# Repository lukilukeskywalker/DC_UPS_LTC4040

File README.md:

# DC_UPS_LTC4040
Low power Uninterrupible Power Supply based on the LTC4040

*The LTC4040 is a complete 3.5V to 5.5V supply rail battery backup system. It contains a high current step-up DC/DC regulator to back up the supply from a single-cell Li-Ion or LiFePO4 battery.*
Picked from the datasheet.

So yeah, This is supposed to be a place in module for Low Power systems that need to keep functioning when power goes off. The dimensions of the module are 30 x 30 mm, and it can be configured (as stated in the datasheet) to support different battery chemistries, and to disable or enable features like Overvoltage protection or Temperature Control of the battery

Everything is described in the schematic:

And the board design is Included:

The board hasn't been tested yet, so take with care. 
Also I do not take any responsability or problems that may arrise with its use

### Proyects that may arrise Interest to the readers:
- [The Ultimate Single Cell Lithium UPS for any Raspberry Pi](https://hackaday.io/project/162653/logs?sort=oldest)
- [LTC4040 5V, 2.5A Uninterruptible Power Supply (UPS) with USB-C](https://www.beyondlogic.org/ltc4040-5v-2-5a-uninterruptible-power-supply-ups-with-usb-c/)

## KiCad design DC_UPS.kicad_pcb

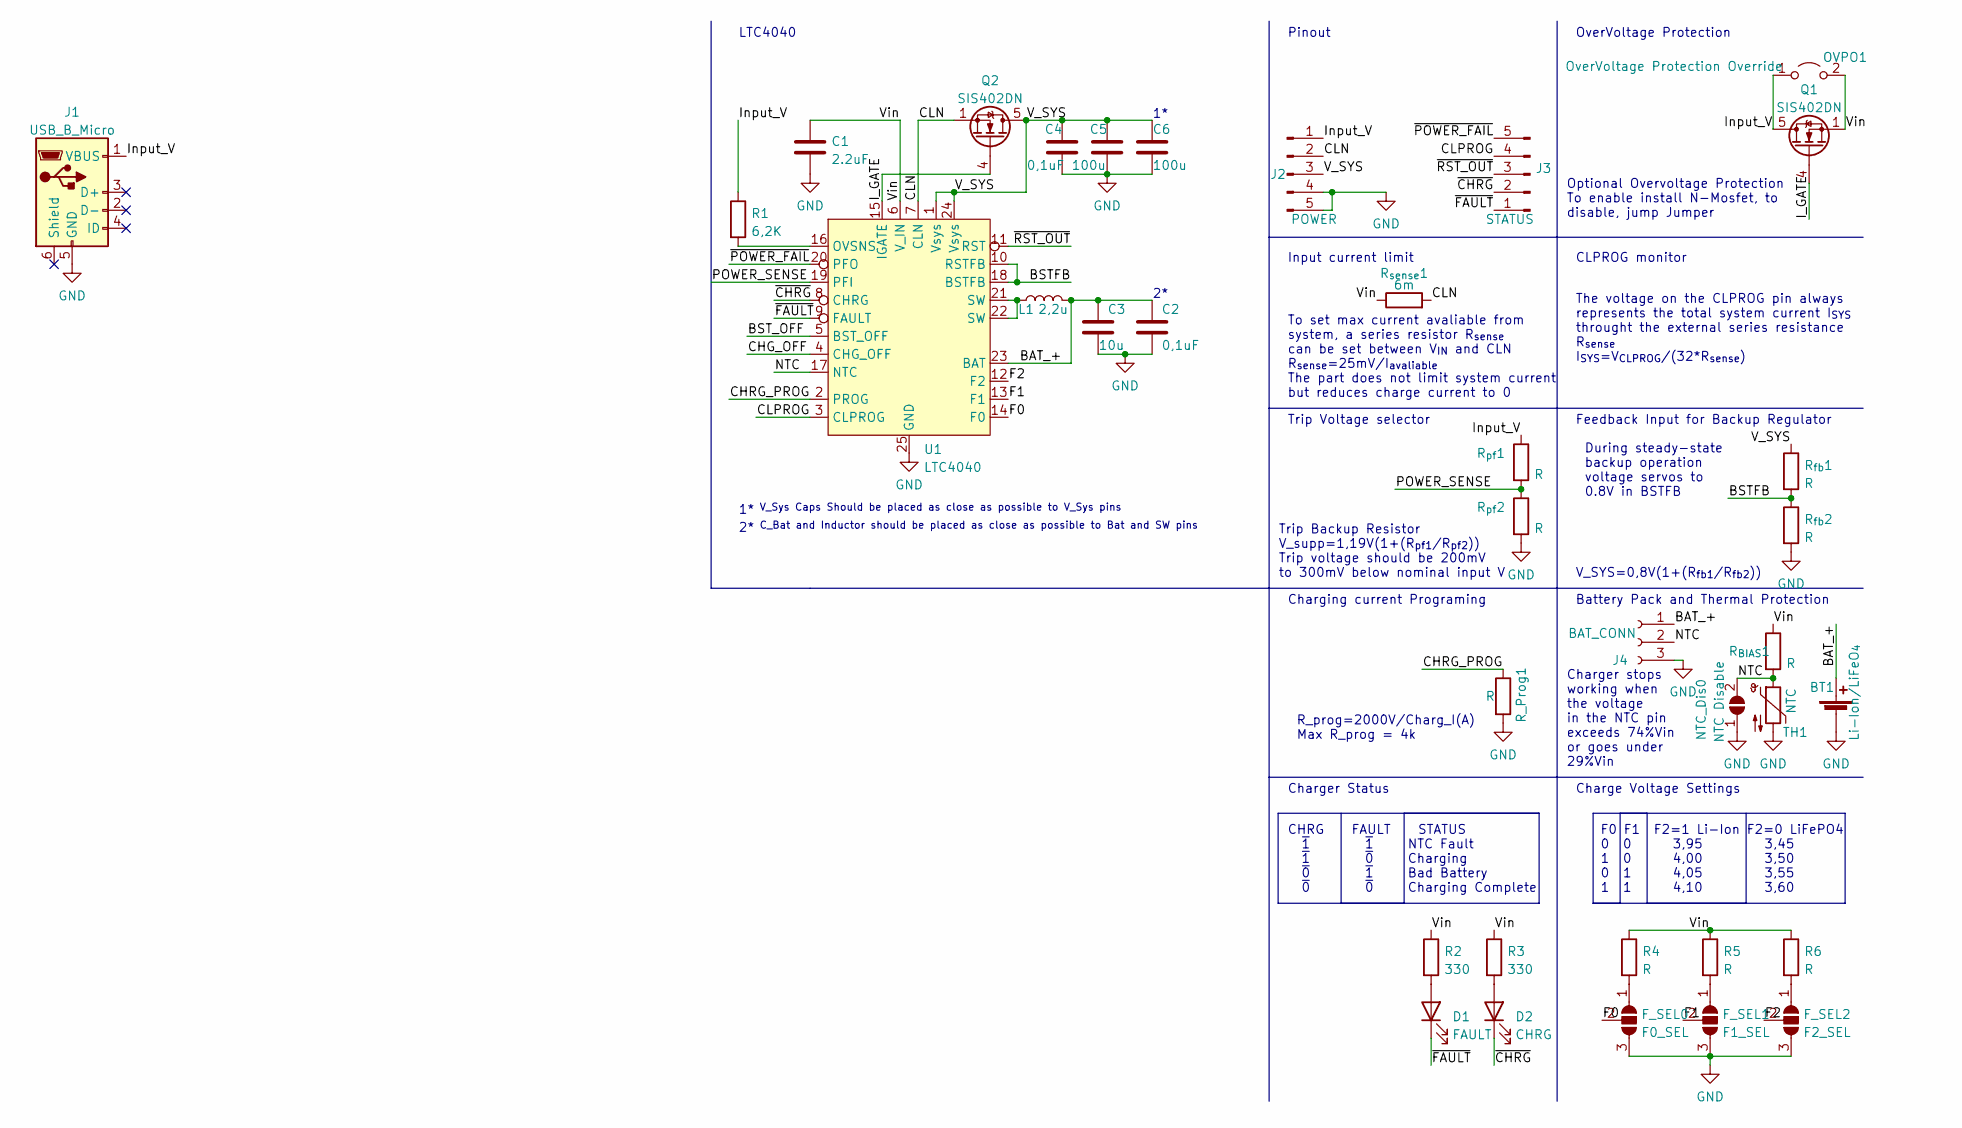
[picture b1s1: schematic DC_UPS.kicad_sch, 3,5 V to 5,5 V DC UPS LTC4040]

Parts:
BT1: Li-Ion/LiFeO_{4}; TE_1776119-2
C1: 2.2uF; C_0402_1005Metric_Pad0.74x0.62mm_HandSolder
C2, C4: 0,1uF; C_0402_1005Metric_Pad0.74x0.62mm_HandSolder
C3: 10u; C_0805_2012Metric_Pad1.18x1.45mm_HandSolder
C5, C6: 100u; C_1206_3216Metric_Pad1.33x1.80mm_HandSolder
D1: FAULT; LED_1206_3216Metric_Pad1.42x1.75mm_HandSolder
D2: CHRG; LED_1206_3216Metric_Pad1.42x1.75mm_HandSolder
F_SEL0: F0_SEL; SolderJumper-3_P1.3mm_Bridged2Bar12_RoundedPad1.0x1.5mm
F_SEL1: F1_SEL; SolderJumper-3_P1.3mm_Bridged2Bar12_RoundedPad1.0x1.5mm
F_SEL2: F2_SEL; SolderJumper-3_P1.3mm_Bridged2Bar12_RoundedPad1.0x1.5mm
J1: USB_B_Micro; TE_2013499-1
J2: POWER; CastellatedPinHeader_2.54mm_5
J3: STATUS; CastellatedPinHeader_2.54mm_5
J4: BAT_CONN; JST_SH_BM03B-SRSS-TB_1x03-1MP_P1.00mm_Vertical
L1: 2,2u; L_Wuerth_HCI-7030
NTC_Dis0: NTC Disable; SolderJumper-2_P1.3mm_Open_RoundedPad1.0x1.5mm
OVPO1: OverVoltage Protection Override; SolderJumper-2_P1.3mm_Open_RoundedPad1.0x1.5mm
Q1, Q2: SIS402DN; Vishay_PowerPAK_1212-8_Single
R1: 6,2K; R_1206_3216Metric_Pad1.30x1.75mm_HandSolder
R2, R3: 330; R_1206_3216Metric_Pad1.30x1.75mm_HandSolder
R4, R5, R6: R; R_1206_3216Metric_Pad1.30x1.75mm_HandSolder
R_Prog1: R; R_1206_3216Metric_Pad1.30x1.75mm_HandSolder
R_{BIAS}1: R; R_1206_3216Metric_Pad1.30x1.75mm_HandSolder
R_{fb}1, R_{fb}2: R; R_1206_3216Metric_Pad1.30x1.75mm_HandSolder
R_{pf}1, R_{pf}2: R; R_1206_3216Metric_Pad1.30x1.75mm_HandSolder
R_{sense}1: 6m; R_1206_3216Metric_Pad1.30x1.75mm_HandSolder
TH1: NTC; R_Axial_DIN0204_L3.6mm_D1.6mm_P2.54mm_Vertical
U1: LTC4040; QFN-24-1EP_4x5mm_P0.5mm_EP2.65x3.65mm_ThermalVias

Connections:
/BAT_+: BT1.1 (+), C2.1, C3.1, J4.1, L1.2, U1.23 (BAT)
/BSTFB: R_{fb}1.2, R_{fb}2.1, U1.10 (RSTFB), U1.18 (BSTFB)
/BST_OFF: U1.5 (BST_OFF)
/CHG_OFF: U1.4 (CHG_OFF)
/CHRG_PROG: R_Prog1.1, U1.2 (PROG)
/CLN: J2.2, Q2.1 (S), Q2.2 (S), Q2.3 (S), R_{sense}1.2, U1.7 (CLN)
/CLPROG: J3.4, U1.3 (CLPROG)
/F0: F_SEL0.2 (C), U1.14 (F0)
/F1: F_SEL1.2 (C), U1.13 (F1)
/F2: F_SEL2.2 (C), U1.12 (F2)
/I_GATE: Q1.4 (G), Q2.4 (G), U1.15 (IGATE)
/Input_V: J1.1 (VBUS), J2.1, OVPO1.1 (A), Q1.5 (D), R1.1, R_{pf}1.1
/NTC: J4.2, NTC_Dis0.2 (B), R_{BIAS}1.2, TH1.1, U1.17 (NTC)
/POWER_SENSE: R_{pf}1.2, R_{pf}2.1, U1.19 (PFI)
/V_SYS: C4.1, C5.1, C6.1, J2.3, Q2.5 (D), R_{fb}1.1, U1.1 (Vsys), U1.24 (Vsys)
/Vin: C1.1, OVPO1.2 (B), Q1.1 (S), Q1.2 (S), Q1.3 (S), R2.1, R3.1, R4.1, R5.1, R6.1, R_{BIAS}1.1, R_{sense}1.1, U1.6 (V_IN)
/~CHRG: D2.1 (K), J3.2, U1.8 (CHRG)
/~FAULT: D1.1 (K), J3.1, U1.9 (FAULT)
/~POWER_FAIL: J3.5, U1.20 (PFO)
/~RST_OUT: J3.3, U1.11 (RST)
GND: BT1.2 (-), C1.2, C2.2, C3.2, C4.2, C5.2, C6.2, F_SEL0.3 (B), F_SEL1.3 (B), F_SEL2.3 (B), J1.5 (GND), J2.4, J2.5, J4.3, NTC_Dis0.1 (A), R_Prog1.2, R_{fb}2.2, R_{pf}2.2, TH1.2, U1.25 (GND)
unnamed: D1.2 (A), R2.2
unnamed: D2.2 (A), R3.2
unnamed: F_SEL0.1 (A), R4.2
unnamed: F_SEL1.1 (A), R5.2
unnamed: F_SEL2.1 (A), R6.2
unnamed: L1.1, U1.21 (SW), U1.22 (SW)
unnamed: R1.2, U1.16 (OVSNS)

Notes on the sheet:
To set max current avaliable from system, a series resistor R_{sense} can be set between V_{IN} and CLN R_{sense}=25mV/I_{avaliable} The part does not limit system current but reduces charge current to 0
Charging current Programing
Charger stops working when the voltage in the NTC pin exceeds 74%Vin or goes under 29%Vin
CHRG FAULT STATUS ~{1} ~{1} NTC Fault ~{1} ~{0} Charging ~{0} ~{1} Bad Battery ~{0} ~{0} Charging Complete
During steady-state backup operation voltage servos to 0.8V in BSTFB
F0 F1 F2=1 Li-Ion F2=0 LiFePO4 0 0 3,95 3,45 1 0 4,00 3,50 0 1 4,05 3,55 1 1 4,10 3,60
1*^{ V_Sys Caps Should be placed as close as possible to V_Sys pins}
Charge Voltage Settings
Input current limit
Charger Status
V_SYS=0,8V(1+(R_{fb1}/R_{fb2}))
Trip Voltage selector
Optional Overvoltage Protection To enable install N-Mosfet, to disable, jump Jumper
LTC4040
CLPROG monitor
Trip Backup Resistor V_supp=1,19V(1+(R_{pf1}/R_{pf2})) Trip voltage should be 200mV to 300mV below nominal input V
Battery Pack and Thermal Protection
The voltage on the CLPROG pin always represents the total system current I_{SYS} throught the external series resistance R_{sense} I_{SYS}=V_{CLPROG}/(32*R_{sense})
Feedback Input for Backup Regulator
2*^{ C_Bat and Inductor should be placed as close as possible to Bat and SW pins}
Pinout
OverVoltage Protection
R_prog=2000V/Charg_I(A) Max R_prog = 4k

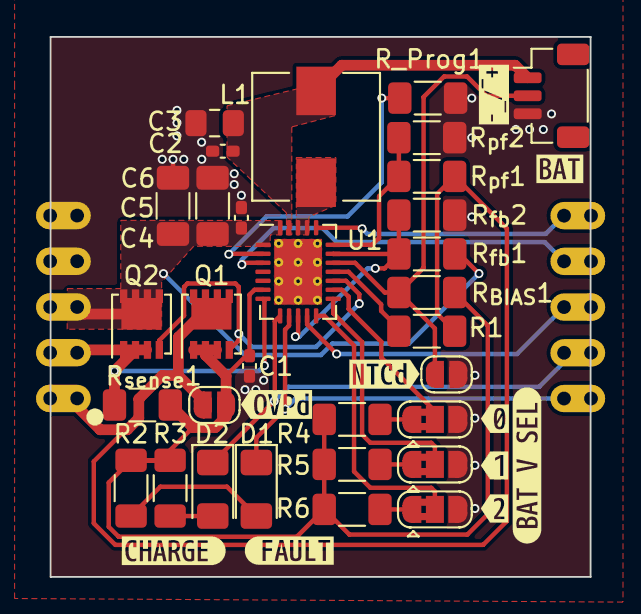
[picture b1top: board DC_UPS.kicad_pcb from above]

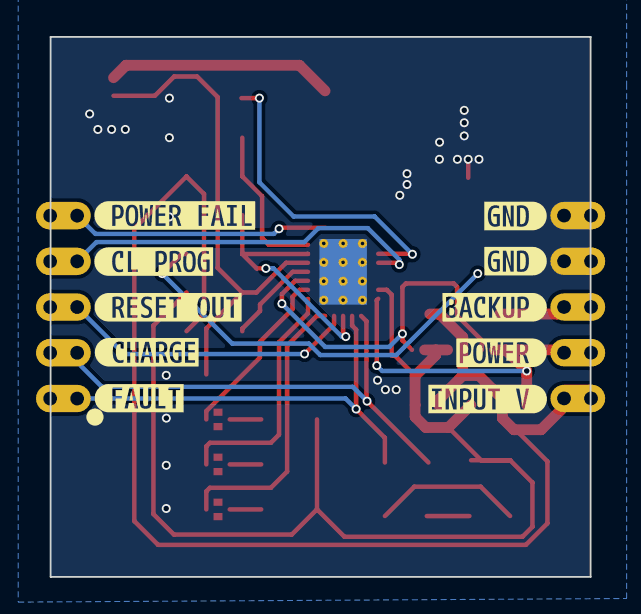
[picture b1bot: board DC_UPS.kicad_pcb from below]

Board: 2 copper layers, 30.0 x 30.0 mm, 53 parts (11 on the bottom side), 26 nets.

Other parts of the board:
kibuzzard-63A1A2AA: G***; kibuzzard-63A1A2AA
kibuzzard-63A1A4C9: G***; kibuzzard-63A1A4C9
kibuzzard-63A1A047: G***; kibuzzard-63A1A047
kibuzzard-63A1A50F: G***; kibuzzard-63A1A50F
kibuzzard-63A1A71E: G***; kibuzzard-63A1A71E
kibuzzard-63A1A72A: G***; kibuzzard-63A1A72A
kibuzzard-63A1A128: G***; kibuzzard-63A1A128
kibuzzard-63A1A287: G***; kibuzzard-63A1A287
kibuzzard-63A1A543: G***; kibuzzard-63A1A543
kibuzzard-63A1A568, kibuzzard-63A1A568#2: G***; kibuzzard-63A1A568
kibuzzard-63A1A734: G***; kibuzzard-63A1A734
kibuzzard-63A1A785: G***; kibuzzard-63A1A785
kibuzzard-63A1A798: G***; kibuzzard-63A1A798
kibuzzard-63A19CFD: G***; kibuzzard-63A19CFD
kibuzzard-63A19D4B: G***; kibuzzard-63A19D4B
kibuzzard-63A19D17: G***; kibuzzard-63A19D17
kibuzzard-63A19E71: G***; kibuzzard-63A19E71
kibuzzard-63A19F8A: G***; kibuzzard-63A19F8A
kibuzzard-63A19F98: G***; kibuzzard-63A19F98

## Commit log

2022-12-12 [Schematic] Initial commit
2022-12-15 [Board]Build board without connectors
2022-12-20 [Board]Finish product rev 1
2022-12-25 [Board][Readme]Update
